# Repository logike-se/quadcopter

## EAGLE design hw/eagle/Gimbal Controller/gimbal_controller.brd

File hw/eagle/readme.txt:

Gimbal Controller v1 will no longer be developed.
Will use version 2 instead, more suitible components

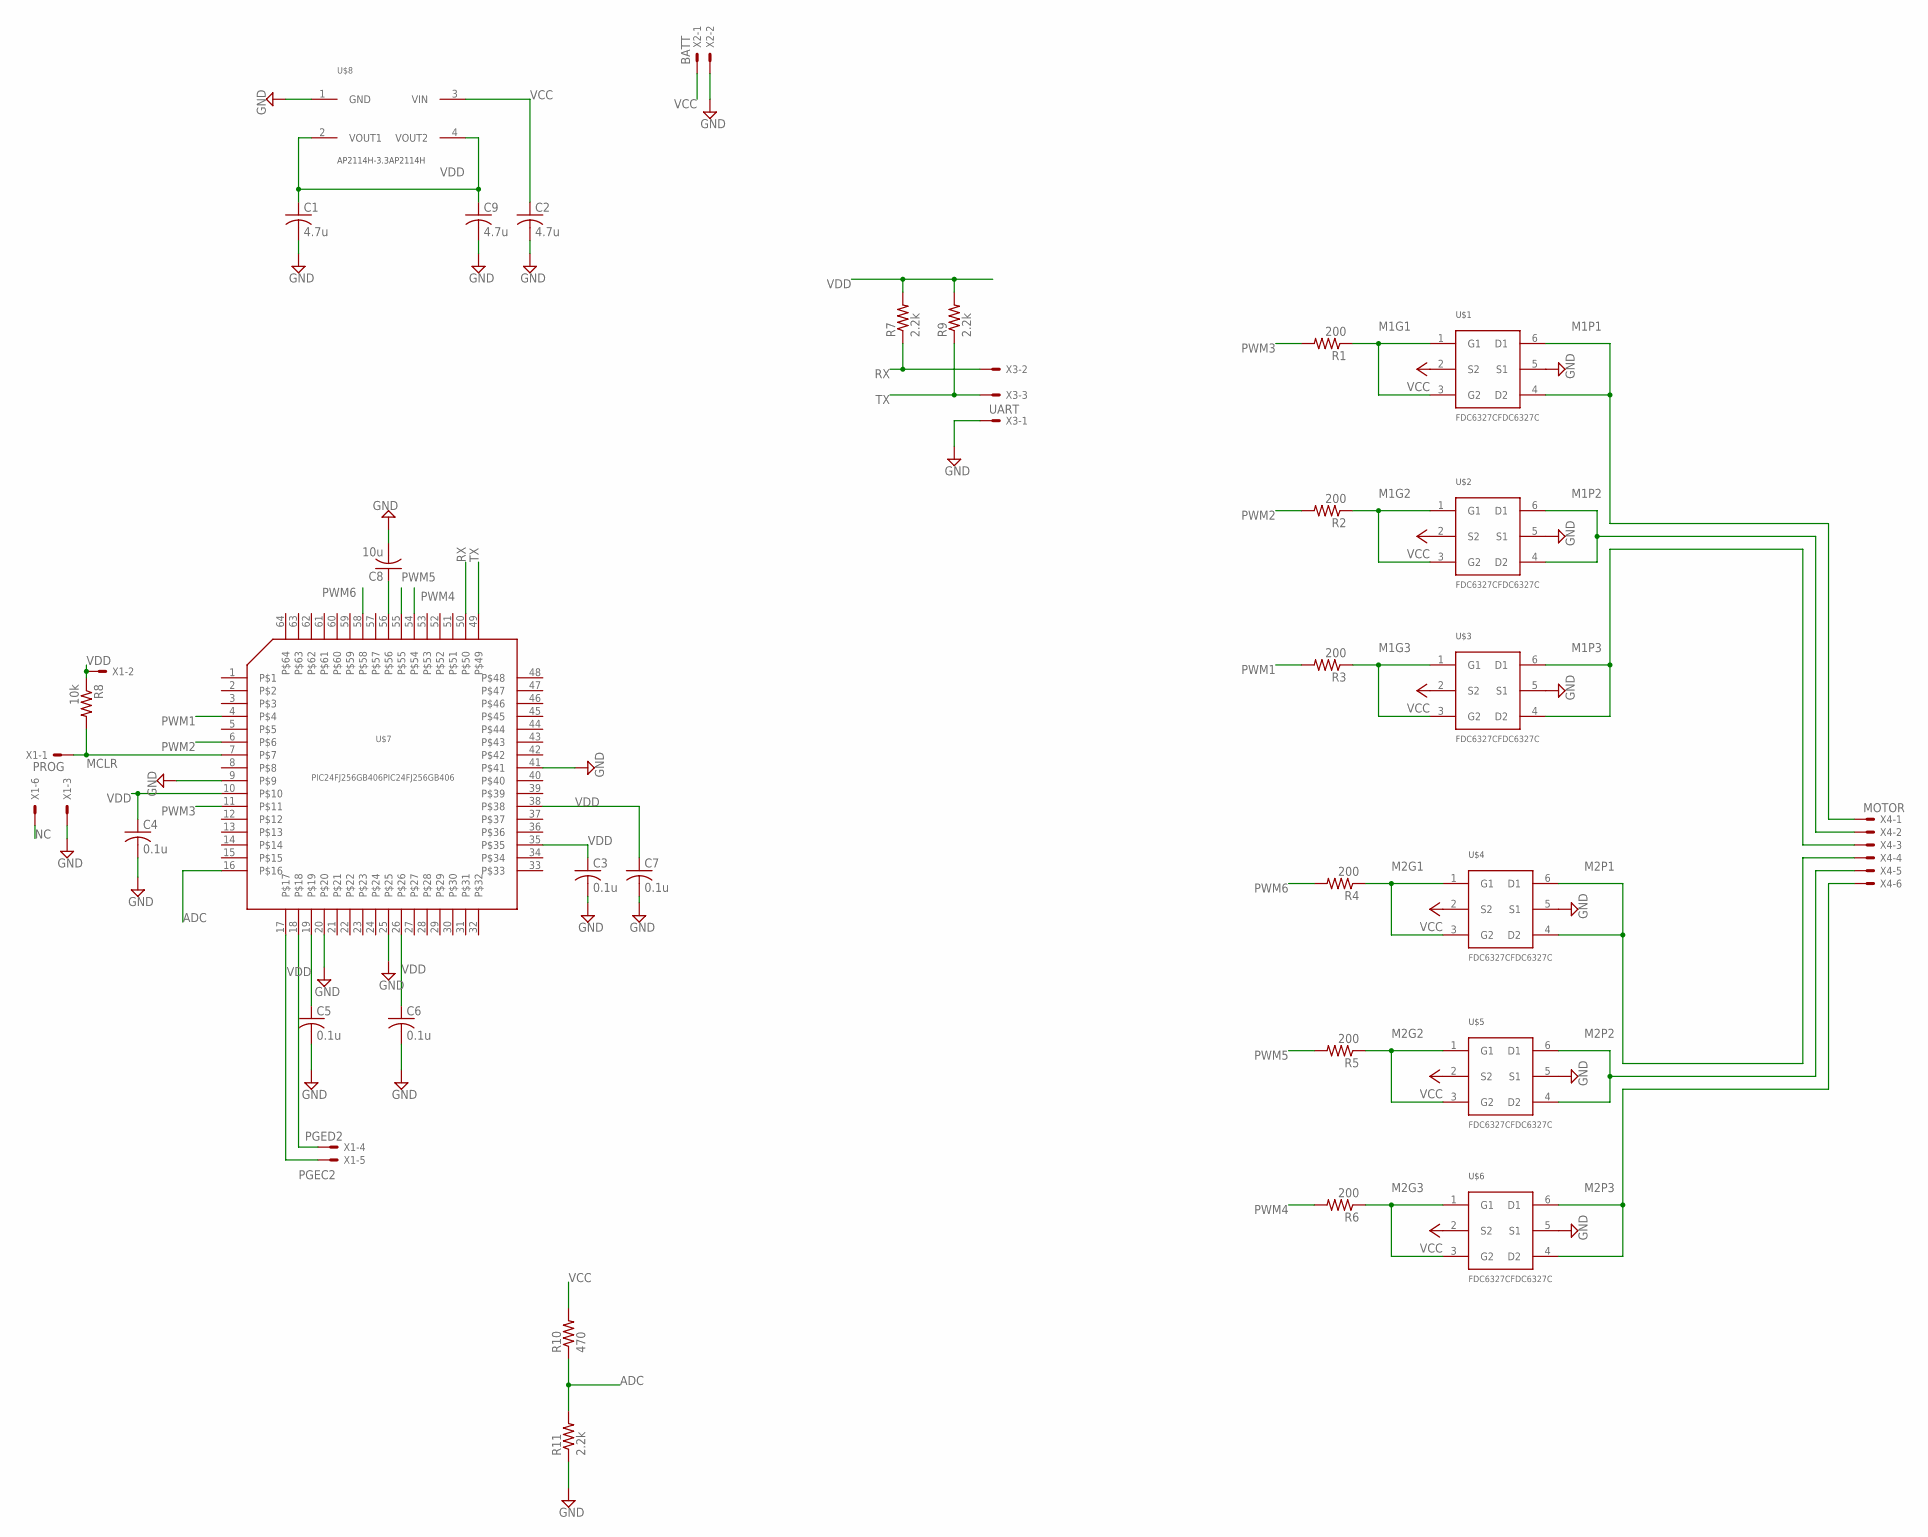
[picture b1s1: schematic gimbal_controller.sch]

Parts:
C1, C2, C9: 4.7u; C0805
C3, C4, C5, C6, C7: 0.1u; C0805
C8: 10u; C0805
R1, R2, R3, R4, R5, R6: 200; R0805
R7, R9, R11: 2.2k; R0805
R8: 10k; R0805
R10: 470; R0805
U$1, U$2, U$3, U$4, U$5, U$6: FDC6327CFDC6327C; SSOT6
U$7: PIC24FJ256GB406PIC24FJ256GB406; TQFP64-10X10
U$8: AP2114H-3.3AP2114H; SOT223
X1: PROG; 22-23-2061
X2: BATT; 22-23-2021
X3: UART; 22-23-2031
X4: MOTOR; 22-23-2061

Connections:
ADC: R10.1, R11.2, U$7.16
GND: C1.2, C2.2, C3.2, C4.2, C5.2, C6.2, C7.2, C8.2, C9.2, R11.1, U$1.5 (S1), U$2.5 (S1), U$3.5 (S1), U$4.5 (S1), U$5.5 (S1), U$6.5 (S1), U$7.9, U$7.20, U$7.25, U$7.41, U$8.1 (GND), X1.3, X2.2, X3.1
M1G1: R1.1, U$1.1 (G1), U$1.3 (G2)
M1G2: R2.1, U$2.1 (G1), U$2.3 (G2)
M1G3: R3.1, U$3.1 (G1), U$3.3 (G2)
M1P1: U$1.4 (D2), U$1.6 (D1), X4.1
M1P2: U$2.4 (D2), U$2.6 (D1), X4.2
M1P3: U$3.4 (D2), U$3.6 (D1), X4.3
M2G1: R4.1, U$4.1 (G1), U$4.3 (G2)
M2G2: R5.1, U$5.1 (G1), U$5.3 (G2)
M2G3: R6.1, U$6.1 (G1), U$6.3 (G2)
M2P1: U$4.4 (D2), U$4.6 (D1), X4.4
M2P2: U$5.4 (D2), U$5.6 (D1), X4.5
M2P3: U$6.4 (D2), U$6.6 (D1), X4.6
MCLR: R8.2, U$7.7, X1.1
unnamed: C8.1, U$7.56
NC: X1.6
PGEC2: U$7.17, X1.5
PGED2: U$7.18, X1.4
PWM1: R3.2, U$7.4
PWM2: R2.2, U$7.6
PWM3: R1.2, U$7.11
PWM4: R6.2, U$7.54
PWM5: R5.2, U$7.55
PWM6: R4.2, U$7.58
RX: R7.1, U$7.50, X3.2
TX: R9.1, U$7.49, X3.3
VCC: C2.1, R10.2, U$1.2 (S2), U$2.2 (S2), U$3.2 (S2), U$4.2 (S2), U$5.2 (S2), U$6.2 (S2), U$8.3 (VIN), X2.1
VDD: C1.1, C3.1, C4.1, C5.1, C6.1, C7.1, C9.1, R7.2, R8.1, R9.2, U$7.10, U$7.19, U$7.26, U$7.35, U$7.38, U$8.2 (VOUT1), U$8.4 (VOUT2), X1.2

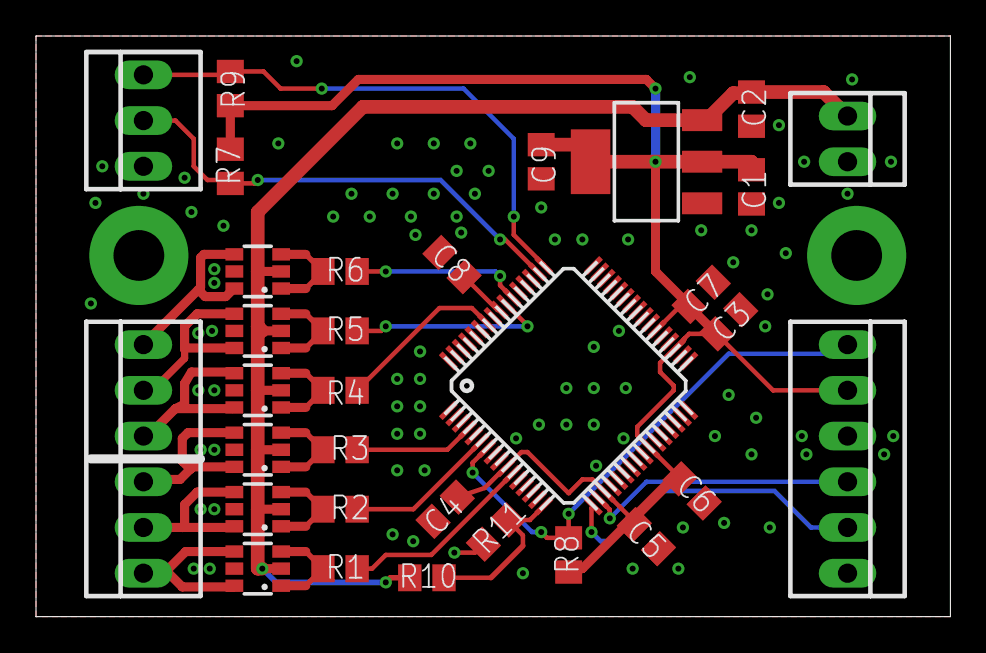
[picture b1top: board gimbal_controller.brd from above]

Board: 2 copper layers, 50.8 x 32.3 mm, 32 parts (0 on the bottom side), 28 nets.

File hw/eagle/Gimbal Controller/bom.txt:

Partlist exported from /Users/johanwestlund/quadcopter/hw/eagle/Gimbal Controller/gimbal_controller.sch at 01/02/16 21:35

Part Value                          Device                         Package      Description                          DIGIKEY_PARTNO          MF    MPN        OC_FARNELL OC_NEWARK
C1   4.7u                           C-USC0805                      C0805        CAPACITOR, American symbol                                                                        
C2   4.7u                           C-USC0805                      C0805        CAPACITOR, American symbol                                                                        
C3   0.1u                           C-USC0805                      C0805        CAPACITOR, American symbol                                                                        
C4   0.1u                           C-USC0805                      C0805        CAPACITOR, American symbol                                                                        
C5   0.1u                           C-USC0805                      C0805        CAPACITOR, American symbol                                                                        
C6   0.1u                           C-USC0805                      C0805        CAPACITOR, American symbol                                                                        
C7   0.1u                           C-USC0805                      C0805        CAPACITOR, American symbol                                                                        
C8   10u                            C-USC0805                      C0805        CAPACITOR, American symbol                                                                        
C9   4.7u                           C-USC0805                      C0805        CAPACITOR, American symbol                                                                        
R1   200                            R-US_R0805                     R0805        RESISTOR, American symbol                                                                         
R2   200                            R-US_R0805                     R0805        RESISTOR, American symbol                                                                         
R3   200                            R-US_R0805                     R0805        RESISTOR, American symbol                                                                         
R4   200                            R-US_R0805                     R0805        RESISTOR, American symbol                                                                         
R5   200                            R-US_R0805                     R0805        RESISTOR, American symbol                                                                         
R6   200                            R-US_R0805                     R0805        RESISTOR, American symbol                                                                         
R7   2k                             R-US_R0805                     R0805        RESISTOR, American symbol                                                                         
R8   10k                            R-US_R0805                     R0805        RESISTOR, American symbol                                                                         
R9   2k                             R-US_R0805                     R0805        RESISTOR, American symbol                                                                         
R10  1.54k                          R-US_R0805                     R0805        RESISTOR, American symbol                                                                         
R11  2k                             R-US_R0805                     R0805        RESISTOR, American symbol                                                                         
U$1  FDC6327CFDC6327C               FDC6327CFDC6327C               SSOT6        MOSFET N/P HALFBRIDGE                FDC6327CCT-ND                                                
U$2  FDC6327CFDC6327C               FDC6327CFDC6327C               SSOT6        MOSFET N/P HALFBRIDGE                FDC6327CCT-ND                                                
U$3  FDC6327CFDC6327C               FDC6327CFDC6327C               SSOT6        MOSFET N/P HALFBRIDGE                FDC6327CCT-ND                                                
U$4  FDC6327CFDC6327C               FDC6327CFDC6327C               SSOT6        MOSFET N/P HALFBRIDGE                FDC6327CCT-ND                                                
U$5  FDC6327CFDC6327C               FDC6327CFDC6327C               SSOT6        MOSFET N/P HALFBRIDGE                FDC6327CCT-ND                                                
U$6  FDC6327CFDC6327C               FDC6327CFDC6327C               SSOT6        MOSFET N/P HALFBRIDGE                FDC6327CCT-ND                                                
U$7  PIC24FJ256GB406PIC24FJ256GB406 PIC24FJ256GB406PIC24FJ256GB406 TQFP64-10X10                                      PIC24FJ256GB406-I/PT-ND                                      
U$8  AP2114H-3.3AP2114H             AP2114H-3.3AP2114H             SOT223       IC REG LDO 3.3V 1A SOT223            AP2114H-3.3TRG1DICT-ND                                       
X1   PROG                           22-23-2061                     22-23-2061   .100" (2.54mm) Center Header - 6 Pin                         MOLEX 22-23-2061 1462922    27C1933  
X2   BATT                           22-23-2021                     22-23-2021   .100" (2.54mm) Center Header - 2 Pin                         MOLEX 22-23-2021 1462926    25C3832  
X3   UART                           22-23-2031                     22-23-2031   .100" (2.54mm) Center Header - 3 Pin                         MOLEX 22-23-2031 1462950    30C0862  
X4   MOTOR                          22-23-2061                     22-23-2061   .100" (2.54mm) Center Header - 6 Pin                         MOLEX 22-23-2061 1462922    27C1933

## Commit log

2015-11-21 sync
2015-11-26 Small fixes
2015-11-26 added ignores
2015-11-26 Did some changes with message handling
    When new message is received with sensor data, clone that object before
    sending to next thread for processing.
2015-11-26 Added Filter Thread
    Added a filter thread that will filter incoming sensor values using
    complementary filter. This thread will also synchronise sensor data
    from different sensors using their timestamps.
    Also moved the cloning part to the sensor thread instead.
2016-01-30 Added Gimbal PCB
2016-01-30 fixed libraries
2016-01-30 Added DRC file
2016-01-30 changed folder structure
2016-01-30 renamed folder
2016-01-30 removed project
2016-01-30 re-added project
2016-01-30 added all Names to board
2016-02-01 changed library structure
2016-02-01 removed crap files
2016-02-01 fixed schematic and board with new libraries
2016-02-01 added ignore file
2016-02-01 removed ignore files
2016-02-01 added bom
2016-02-01 fixed some stuff
2016-02-25 fixed board edges and added spice simulation for MOSFETs
2016-02-25 added lt spice simulation
2016-05-21 minor change
2016-05-21 made MPLAB happy
2016-05-21 minor fixes
    - increased drill hole size on connectors
    - changed all text to stop layer instead of overlay, so that the text
    is seen in gold
2016-05-21 added configuration bits
2016-07-12 added some pic24 code
2016-07-26 Added some routing
2016-07-26 Updated pin drill size
2016-07-26 Change PWM to SCCP & MCCP
2016-07-27 refactored some stuff
2016-07-30 added pwm init
2016-08-04 Init PWM at 10kHz
2016-08-09 Version 2
2016-08-15 added new version of gimbal controller
2016-08-15 test
2016-08-15 gitignore test
2016-08-15 added readme
